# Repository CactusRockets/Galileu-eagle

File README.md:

# Placas da aviônica para o foguete Galileu

Nesse repositório temos os arquivos das placas que fizeram parte da aviônica do foguete Galileu da Cactus Rockets Design.

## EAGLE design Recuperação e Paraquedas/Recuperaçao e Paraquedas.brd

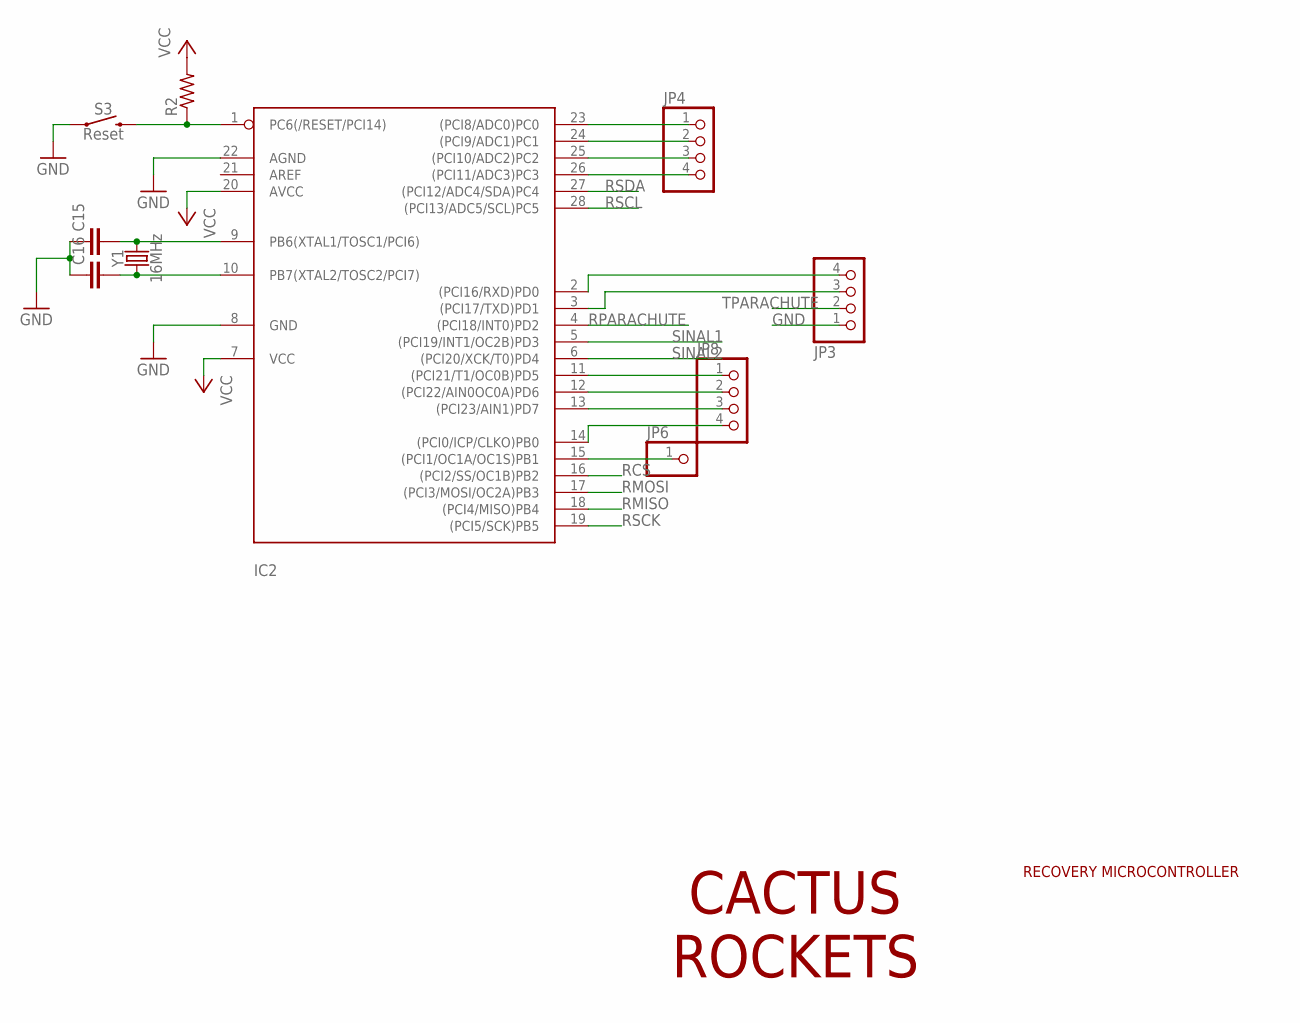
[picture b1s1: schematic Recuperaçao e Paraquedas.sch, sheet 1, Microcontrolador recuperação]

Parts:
C15, C16: C-EU025-025X050; C025-025X050
IC2: ATMEGA328-20P; DIL28-3
JP3: PINHD-1X4/90; 1X04/90
JP4, JP8: PINHD-1X4; 1X04
JP6: PINHD-1X1; 1X01
R2: R-US_0207/10; 0207/10
S3: Reset; TACTILE_SWITCH_PTH_6.0MM
Y1: 16MHz; HC49US

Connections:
GND: C15.1, C16.1, IC2.8 (GND), IC2.22 (AGND), JP3.1, S3.1, S3.2 (1); also elsewhere on the board
unnamed: IC2.23 ((PCI8/ADC0)PC0), JP4.1
unnamed: IC2.24 ((PCI9/ADC1)PC1), JP4.2
unnamed: IC2.25 ((PCI10/ADC2)PC2), JP4.3
unnamed: IC2.26 ((PCI11/ADC3)PC3), JP4.4
unnamed: IC2.2 ((PCI16/RXD)PD0), JP3.4
unnamed: IC2.11 ((PCI21/T1/OC0B)PD5), JP8.1
unnamed: IC2.12 ((PCI22/AIN0OC0A)PD6), JP8.2
unnamed: IC2.13 ((PCI23/AIN1)PD7), JP8.3
unnamed: IC2.15 ((PCI1/OC1A/OC1S)PB1), JP6.1
unnamed: IC2.14 ((PCI0/ICP/CLKO)PB0), JP8.4
unnamed: C16.2, IC2.10 (PB7(XTAL2/TOSC2/PCI7)), Y1.1
unnamed: C15.2, IC2.9 (PB6(XTAL1/TOSC1/PCI6)), Y1.2
unnamed: IC2.3 ((PCI17/TXD)PD1), JP3.3
RCS: IC2.16 ((PCI2/SS/OC1B)PB2); also elsewhere on the board
RESET: IC2.1 (PC6(/RESET/PCI14)), R2.1, S3.3 (2), S3.4 (2)
RMISO: IC2.18 ((PCI4/MISO)PB4); also elsewhere on the board
RMOSI: IC2.17 ((PCI3/MOSI/OC2A)PB3); also elsewhere on the board
RPARACHUTE: IC2.4 ((PCI18/INT0)PD2); also elsewhere on the board
RSCK: IC2.19 ((PCI5/SCK)PB5); also elsewhere on the board
RSCL: IC2.28 ((PCI13/ADC5/SCL)PC5); also elsewhere on the board
RSDA: IC2.27 ((PCI12/ADC4/SDA)PC4); also elsewhere on the board
SINAL1: IC2.5 ((PCI19/INT1/OC2B)PD3); also elsewhere on the board
SINAL2: IC2.6 ((PCI20/XCK/T0)PD4); also elsewhere on the board
TPARACHUTE: JP3.2; also elsewhere on the board
VCC: IC2.7 (VCC), IC2.20 (AVCC), R2.2; also elsewhere on the board

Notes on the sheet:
CACTUS ROCKETS
RECOVERY MICROCONTROLLER

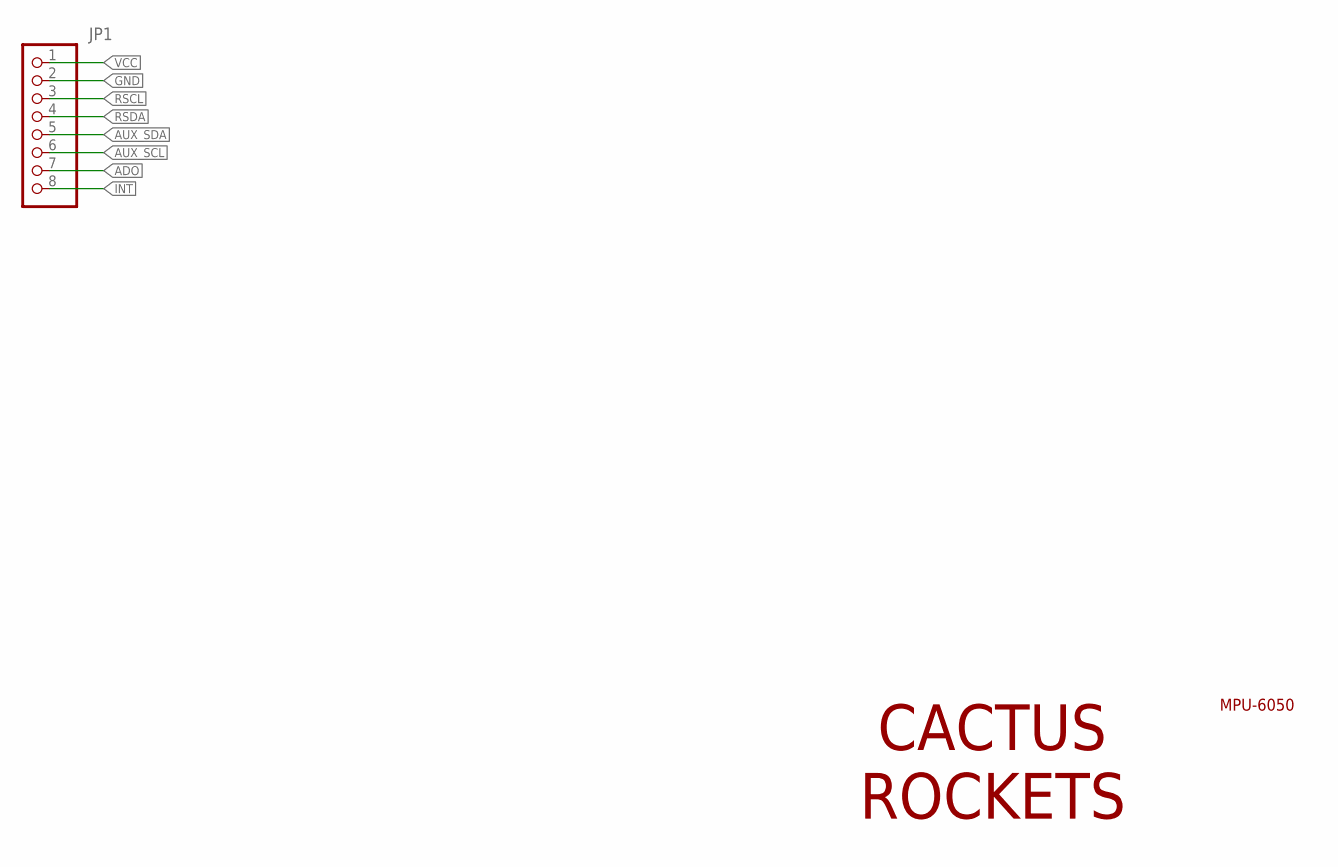
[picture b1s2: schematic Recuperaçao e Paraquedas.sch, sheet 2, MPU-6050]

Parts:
JP1: PINHD-1X8; 1X08

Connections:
ADO: JP1.7
AUX_SCL: JP1.6
AUX_SDA: JP1.5
GND: JP1.2; also elsewhere on the board
INT: JP1.8
RSCL: JP1.3; also elsewhere on the board
RSDA: JP1.4; also elsewhere on the board
VCC: JP1.1; also elsewhere on the board

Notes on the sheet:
CACTUS ROCKETS
MPU-6050

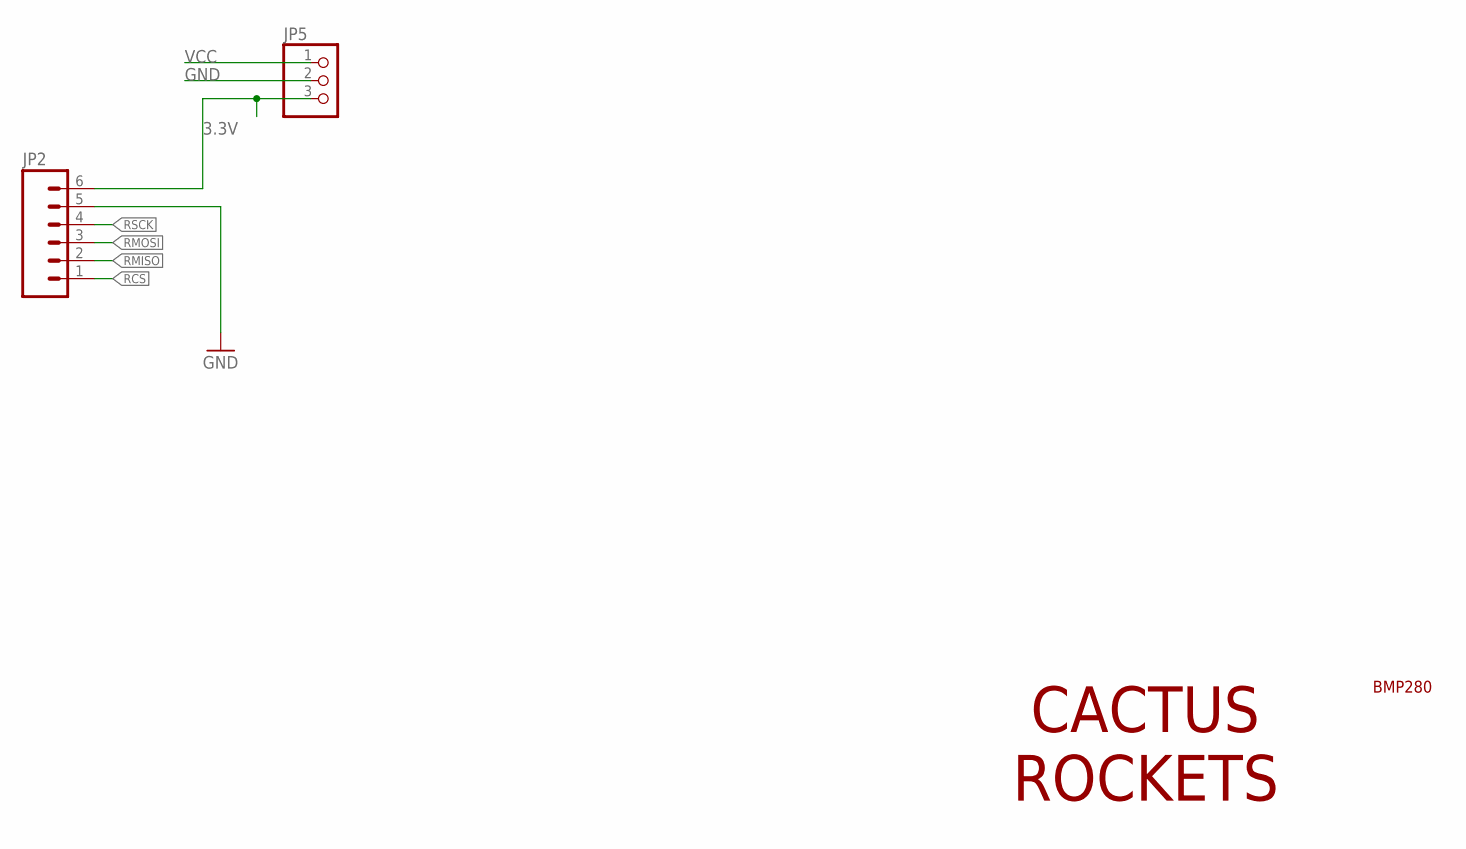
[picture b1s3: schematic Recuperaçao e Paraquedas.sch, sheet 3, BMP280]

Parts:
JP2: M06NO_SILK_FEMALE_PTH; 1X06_NO_SILK
JP5: PINHD-1X3/90; 1X03/90

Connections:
3.3V: JP2.6, JP5.3
GND: JP2.5, JP5.2; also elsewhere on the board
RCS: JP2.1; also elsewhere on the board
RMISO: JP2.2; also elsewhere on the board
RMOSI: JP2.3; also elsewhere on the board
RSCK: JP2.4; also elsewhere on the board
VCC: JP5.1; also elsewhere on the board

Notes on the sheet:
CACTUS ROCKETS
BMP280

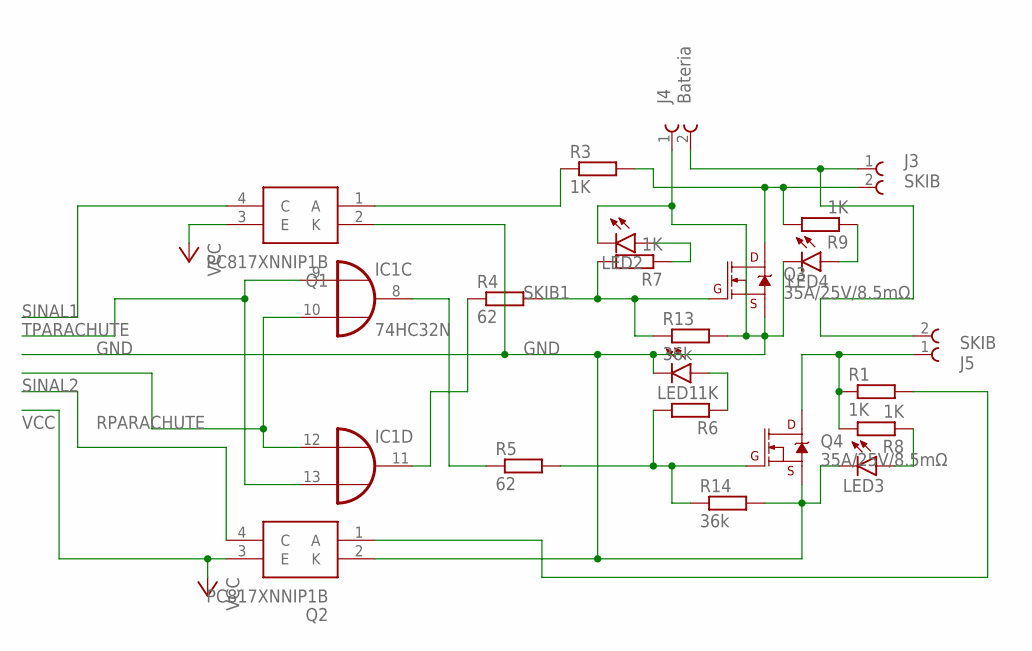
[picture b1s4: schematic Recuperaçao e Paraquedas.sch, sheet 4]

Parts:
IC1: 74HC32N; DIL14
J3, J5: SKIB; 691111710002
J4: Bateria; 691111710002
LED1, LED2, LED3, LED4: LEDCHIP-LED0805; CHIP-LED0805
Q1, Q2: PC817XNNIP1B; SOP254P960X420-4N
Q3, Q4: 35A/25V/8.5mΩ; TO-252/DPAK
R1, R3: 1K; R0603
R4, R5: 62; M0805
R6, R7, R8, R9: 1K; M0805
R13, R14: 36k; M0805

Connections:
GND: IC1.7 (GND), J4.1, LED1.C, LED2.C, LED3.C, LED4.C, Q1.2 (K), Q2.2 (K), Q3.3 (S), Q4.3 (S), R13.2, R14.2; also elsewhere on the board
unnamed: IC1.8 (O), R5.1
unnamed: IC1.11 (O), R4.1
unnamed: Q1.1 (A), R3.1
unnamed: LED4.A, R9.1
unnamed: Q2.1 (A), R1.2
unnamed: J3.1, J4.2, J5.2
unnamed: LED2.A, R7.1
unnamed: LED1.A, R6.1
unnamed: LED3.A, R8.1
unnamed: J5.1, Q4.2 (D), R1.1, R8.2
unnamed: J3.2, Q3.2 (D), R3.2, R9.2
RPARACHUTE: IC1.10 (I1), IC1.12 (I0); also elsewhere on the board
SINAL1: Q1.4 (C); also elsewhere on the board
SINAL2: Q2.4 (C); also elsewhere on the board
SKIB1: Q3.1 (G), R4.2, R7.2, R13.1
SKIB2: Q4.1 (G), R5.2, R6.2, R14.1
TPARACHUTE: IC1.9 (I0), IC1.13 (I1); also elsewhere on the board
VCC: IC1.14 (VCC), Q1.3 (E), Q2.3 (E); also elsewhere on the board

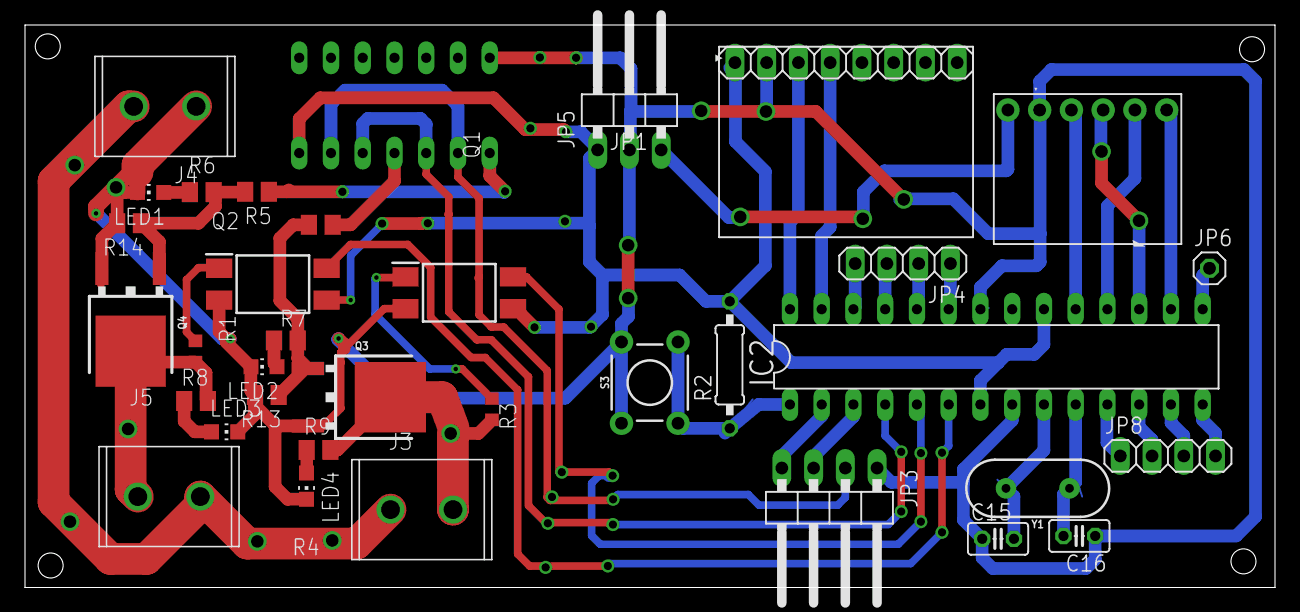
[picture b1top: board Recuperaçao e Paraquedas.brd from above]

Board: 2 copper layers, 100.0 x 45.0 mm, 35 parts (1 on the bottom side), 40 nets.

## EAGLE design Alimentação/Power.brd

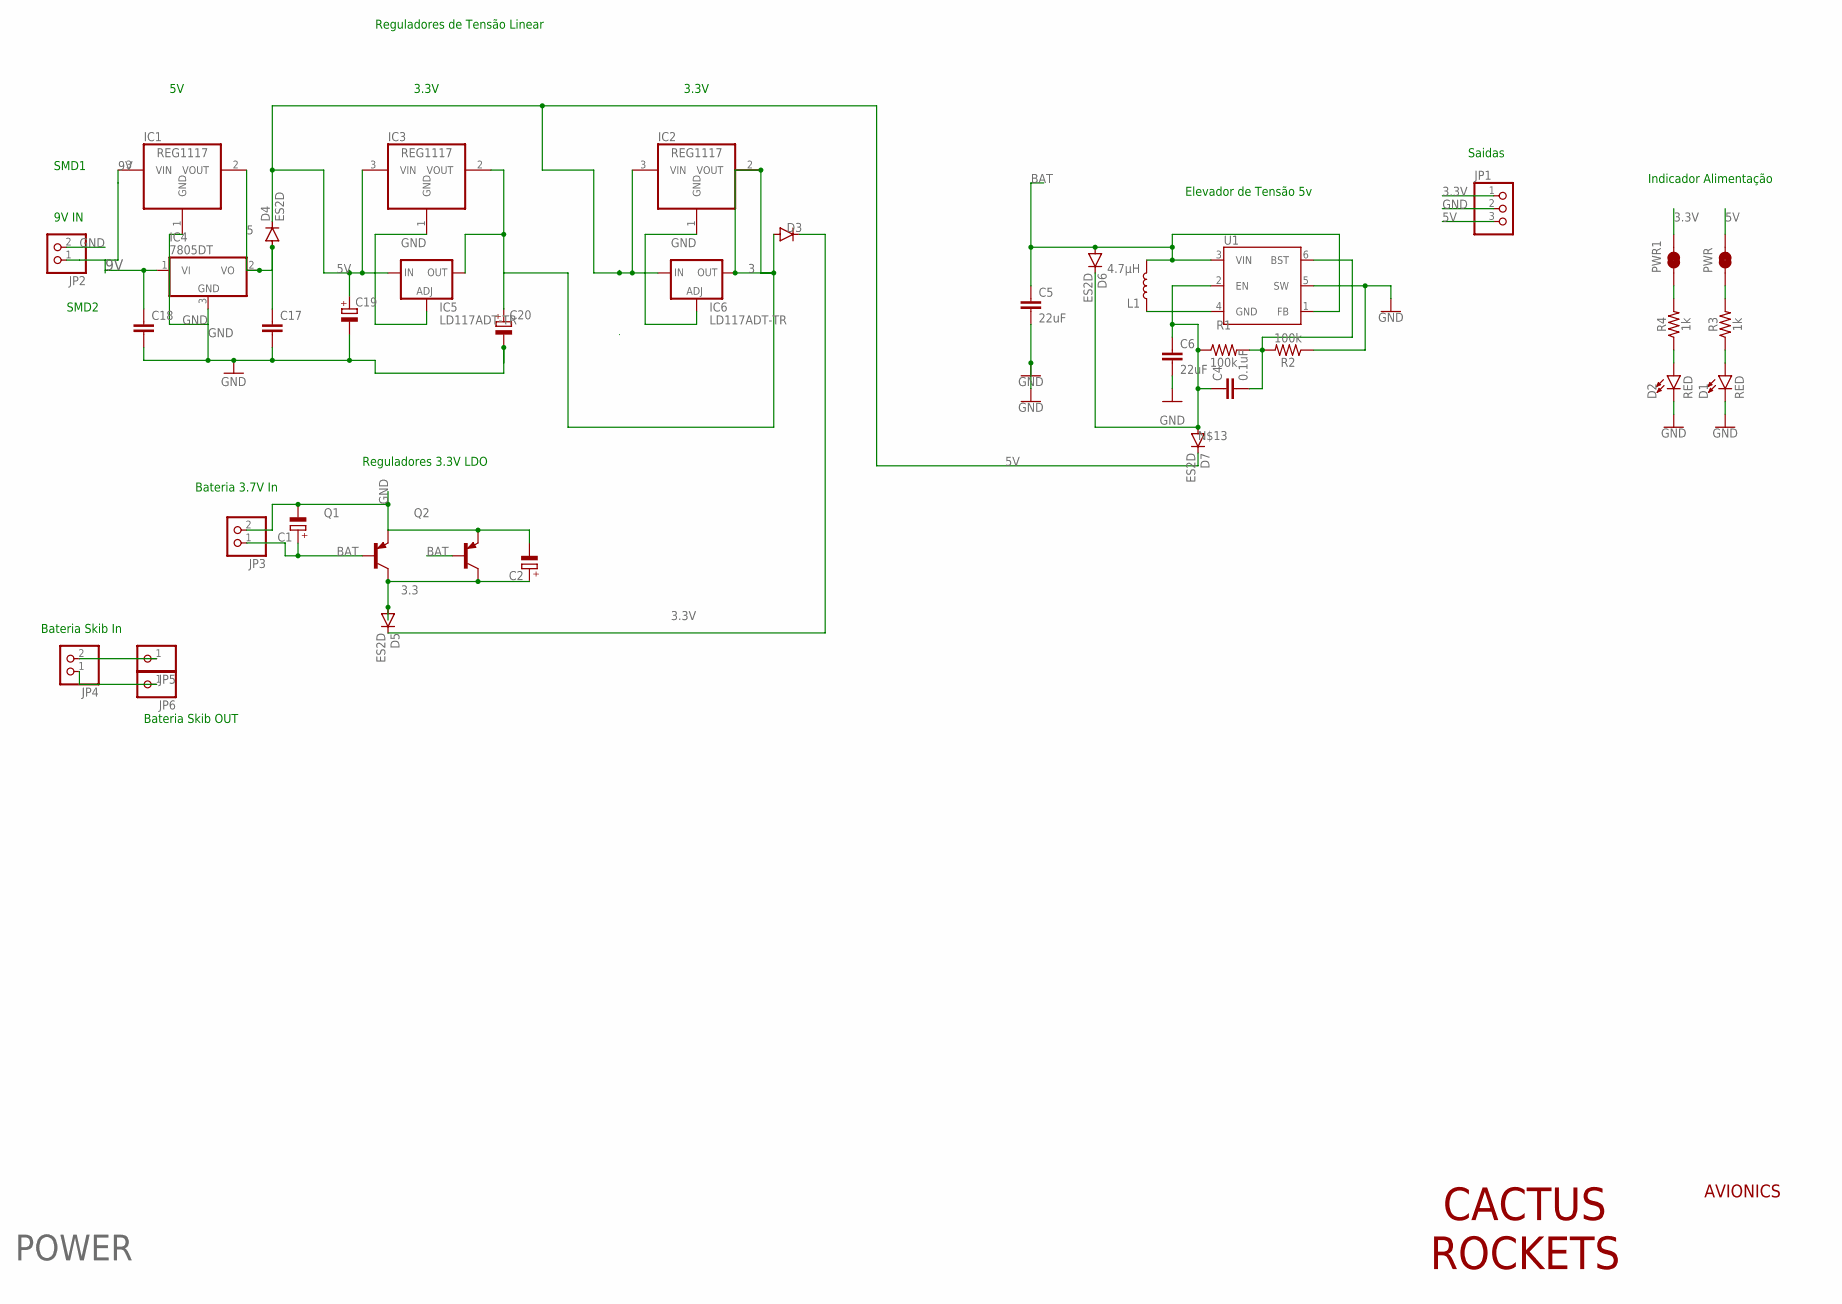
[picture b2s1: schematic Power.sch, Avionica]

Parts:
C1, C2, C19, C20: CPOL-EUE1.8-4; E1,8-4
C4: 0.1uF; 0603
C5, C6: 22uF; 0603
C17, C18: C-EU025-025X050; C025-025X050
D1, D2: RED; LED-0603
D3, D4, D5, D6, D7: ES2D; SMB
IC1, IC2, IC3: REG1117; SOT223
IC4: 7805DT; TO252
IC5, IC6: LD117ADT-TR; DPACK
JP1: PINHD-1X3; 1X03
JP2, JP3, JP4: PINHD-1X2; 1X02
JP5, JP6: PINHD-1X1; 1X01
L1: 4.7μH; INDUCTOR_4X4MM
PWR, PWR1: JUMPER-SMT_2_NC_TRACE_SILK; SMT-JUMPER_2_NC_TRACE_SILK
Q1, Q2: MMBTA56-SOT23; SOT23
R1, R2: 100k; 0603
R3, R4: 1k; 0603
U1: AP63203; SOT23-6

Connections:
3: C20.+, D3.A, IC2.2 (VOUT), IC3.2 (VOUT), IC5.4 (OUT), IC6.4 (OUT)
3.3: C2.+, D5.A, Q1.3 (C), Q2.3 (C)
3.3V: D3.C, D5.C, JP1.1, PWR1.2
5: C17.1, D4.A, IC1.2 (VOUT), IC4.2 (VO)
5V: C19.+, D4.C, D7.C, IC2.3 (VIN), IC3.3 (VIN), IC5.3 (IN), IC6.3 (IN), JP1.3, PWR.2
9V: C18.1, IC1.3 (VIN), IC4.1 (VI), JP2.1
BAT: C1.+, C5.1, D6.A, JP3.1, L1.P$2 (2), Q1.1 (B), Q2.1 (B), U1.1 (FB), U1.3 (VIN)
GND: C1.-, C2.-, C5.2, C6.2, C17.2, C18.2, C19.-, C20.-, D1.C, D2.C, IC1.1 (GND), IC2.1 (GND), IC3.1 (GND), IC4.3 (GND), IC5.1 (ADJ), IC6.1 (ADJ), JP1.2, JP2.2, JP3.2, Q1.2 (E), Q2.2 (E), R2.1, U1.5 (SW)
unnamed: C4.2, R1.2, R2.2, U1.6 (BST)
unnamed: D1.A, R3.1
unnamed: PWR.1, R3.2
unnamed: D2.A, R4.1
unnamed: PWR1.1, R4.2
unnamed: L1.P$1 (1), U1.4 (GND)
unnamed: JP4.2, JP5.1
unnamed: C4.1, C6.1, D6.C, D7.A, R1.1, U1.2 (EN)
unnamed: JP4.1, JP6.1

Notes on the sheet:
CACTUS ROCKETS
AVIONICS
POWER
Indicador Alimentação
Saidas
Elevador de Tensão 5v
9V IN
Bateria 3.7V In
Reguladores 3.3V LDO
SMD1
SMD2
Reguladores de Tensão Linear
3.3V
Bateria Skib In
Bateria Skib OUT

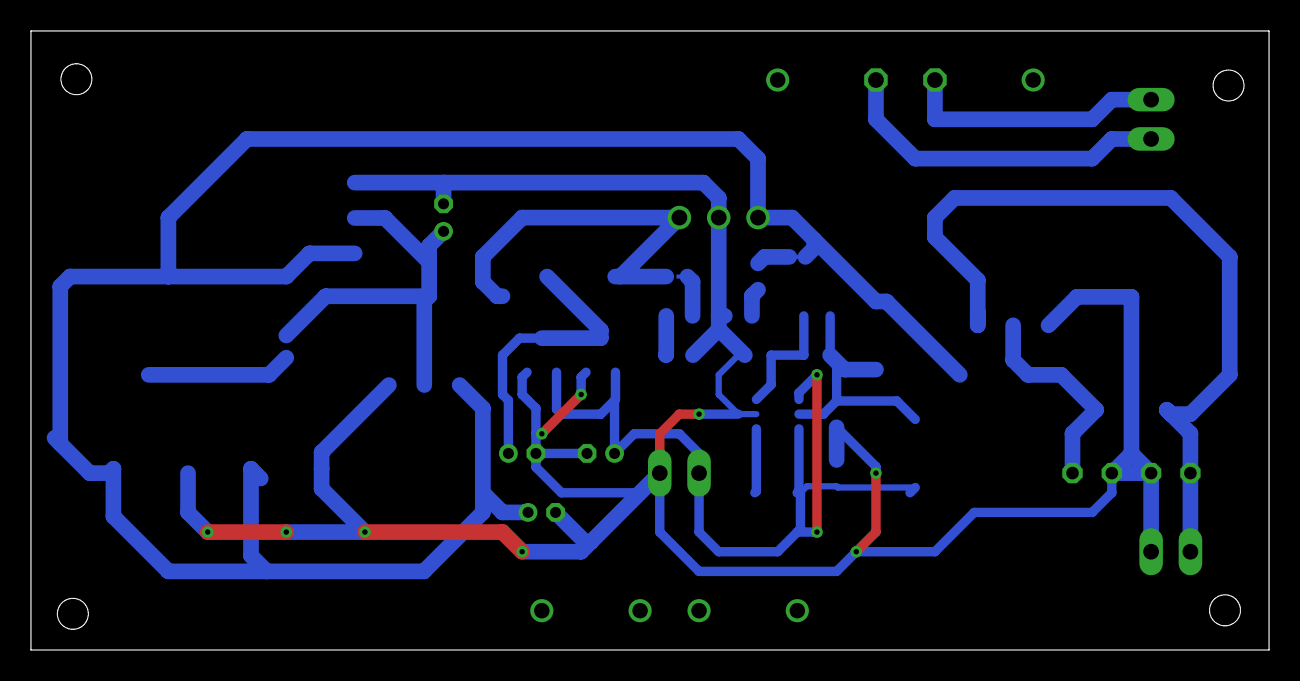
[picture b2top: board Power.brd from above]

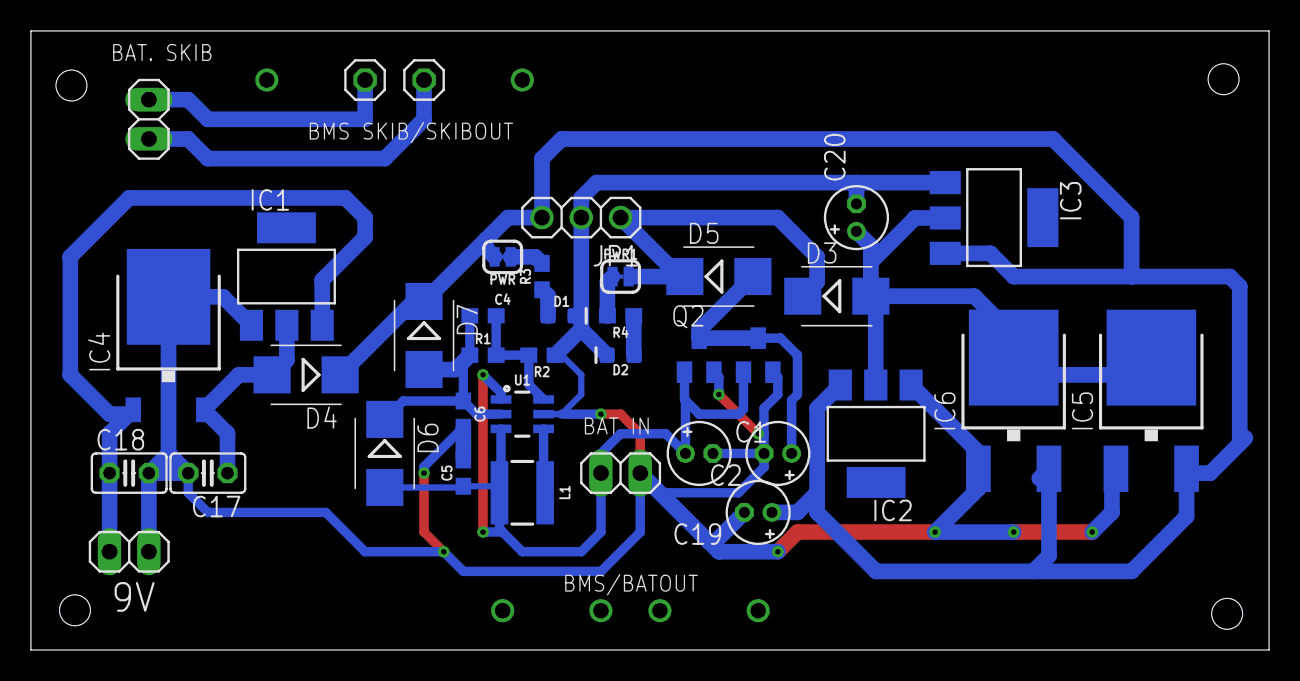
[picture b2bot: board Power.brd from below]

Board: 2 copper layers, 80.0 x 40.0 mm, 38 parts (38 on the bottom side), 17 nets.

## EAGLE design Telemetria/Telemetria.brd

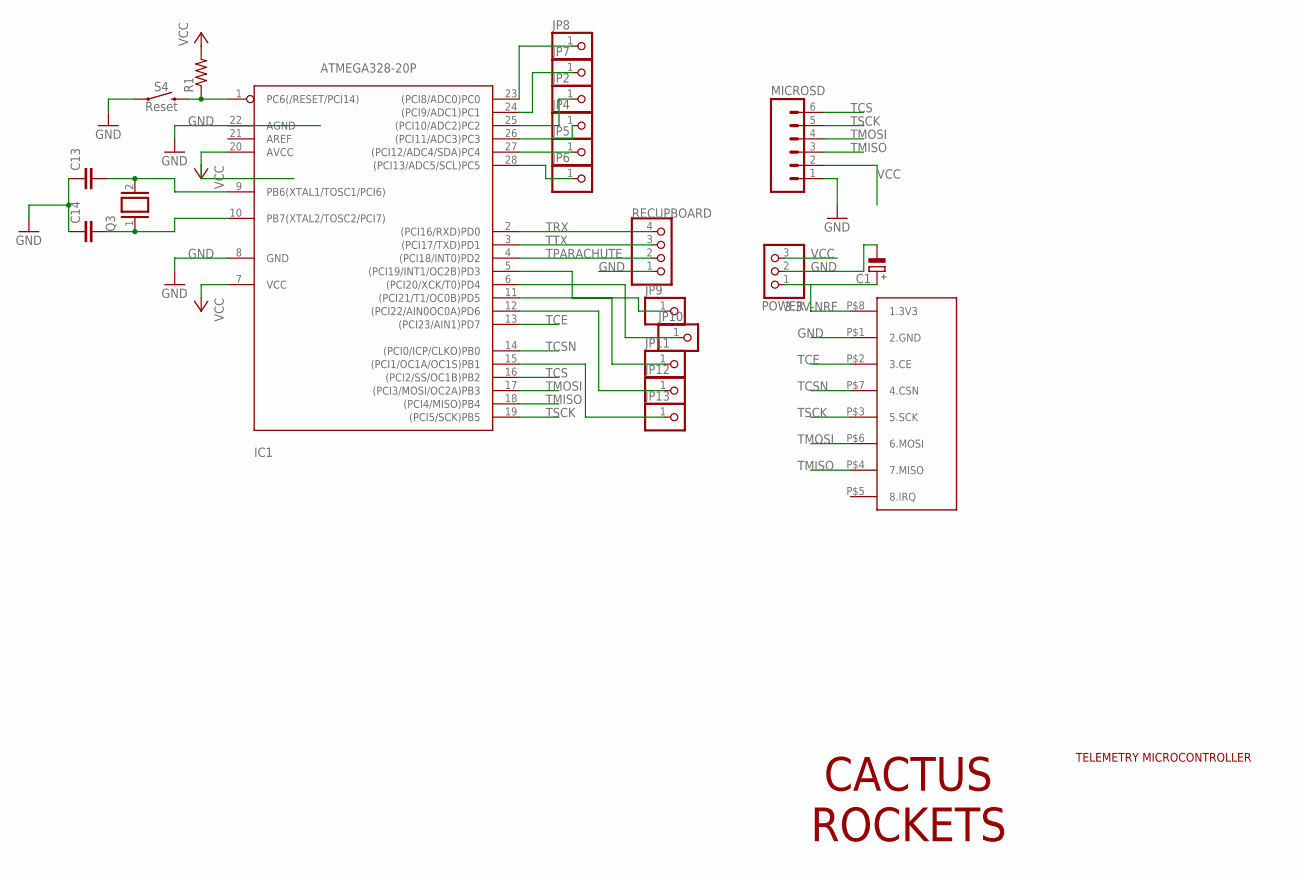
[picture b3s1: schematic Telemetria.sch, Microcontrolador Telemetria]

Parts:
C1: CPOL-EUE1.8-4; E1,8-4
C13, C14: C-EU025-025X050; C025-025X050
IC1: ATMEGA328-20P; DIL28-3
JP2, JP4, JP5, JP6, JP7, JP8, JP9, JP10, JP11, JP12, JP13: PINHD-1X1; 1X01
MICROSD: M06NO_SILK_FEMALE_PTH; 1X06_NO_SILK
POWER: PINHD-1X3/90; 1X03/90
Q3: XTAL/S; QS
R1: R-US_0207/10; 0207/10
RECUPBOARD: PINHD-1X4/90; 1X04/90
S4: Reset; TACTILE_SWITCH_PTH_6.0MM
U$1: NRF24L01+

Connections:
3.3V-NRF: C1.+, POWER.1, U$1.P$8 (1.3V3)
GND: C1.-, C13.1, C14.1, IC1.8 (GND), IC1.22 (AGND), MICROSD.1, POWER.2, RECUPBOARD.1, S4.1, S4.2 (1), U$1.P$1 (2.GND)
unnamed: IC1.23 ((PCI8/ADC0)PC0), JP8.1
unnamed: IC1.24 ((PCI9/ADC1)PC1), JP7.1
unnamed: IC1.25 ((PCI10/ADC2)PC2), JP2.1
unnamed: IC1.26 ((PCI11/ADC3)PC3), JP4.1
unnamed: IC1.27 ((PCI12/ADC4/SDA)PC4), JP5.1
unnamed: IC1.1 (PC6(/RESET/PCI14)), R1.1, S4.3 (2), S4.4 (2)
unnamed: IC1.28 ((PCI13/ADC5/SCL)PC5), JP6.1
unnamed: IC1.5 ((PCI19/INT1/OC2B)PD3), JP9.1
unnamed: IC1.6 ((PCI20/XCK/T0)PD4), JP10.1
unnamed: IC1.11 ((PCI21/T1/OC0B)PD5), JP11.1
unnamed: IC1.12 ((PCI22/AIN0OC0A)PD6), JP12.1
unnamed: IC1.15 ((PCI1/OC1A/OC1S)PB1), JP13.1
unnamed: C14.2, IC1.10 (PB7(XTAL2/TOSC2/PCI7)), Q3.1
unnamed: C13.2, IC1.9 (PB6(XTAL1/TOSC1/PCI6)), Q3.2
TCE: IC1.13 ((PCI23/AIN1)PD7), U$1.P$2 (3.CE)
TCS: IC1.16 ((PCI2/SS/OC1B)PB2), MICROSD.6
TCSN: IC1.14 ((PCI0/ICP/CLKO)PB0), U$1.P$7 (4.CSN)
TMISO: IC1.18 ((PCI4/MISO)PB4), MICROSD.3, U$1.P$4 (7.MISO)
TMOSI: IC1.17 ((PCI3/MOSI/OC2A)PB3), MICROSD.4, U$1.P$6 (6.MOSI)
TPARACHUTE: IC1.4 ((PCI18/INT0)PD2), RECUPBOARD.2
TRX: IC1.2 ((PCI16/RXD)PD0), RECUPBOARD.4
TSCK: IC1.19 ((PCI5/SCK)PB5), MICROSD.5, U$1.P$3 (5.SCK)
TTX: IC1.3 ((PCI17/TXD)PD1), RECUPBOARD.3
VCC: IC1.7 (VCC), IC1.20 (AVCC), MICROSD.2, POWER.3, R1.2

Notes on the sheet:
CACTUS ROCKETS
TELEMETRY MICROCONTROLLER

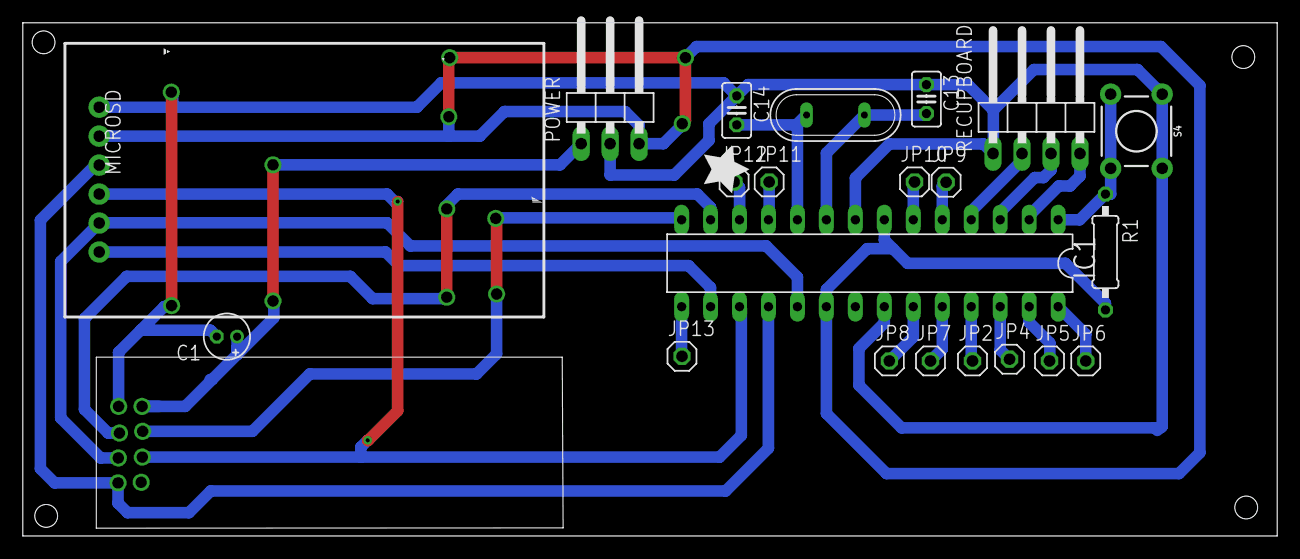
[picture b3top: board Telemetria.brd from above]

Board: 2 copper layers, 110.0 x 45.0 mm, 22 parts (0 on the bottom side), 26 nets.

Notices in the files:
parts and their libraries:
SparkFun-Resistors: Licensing: Creative Commons ShareAlike 4.0 International - https://creativecommons.org/licenses/by-sa/4.0
